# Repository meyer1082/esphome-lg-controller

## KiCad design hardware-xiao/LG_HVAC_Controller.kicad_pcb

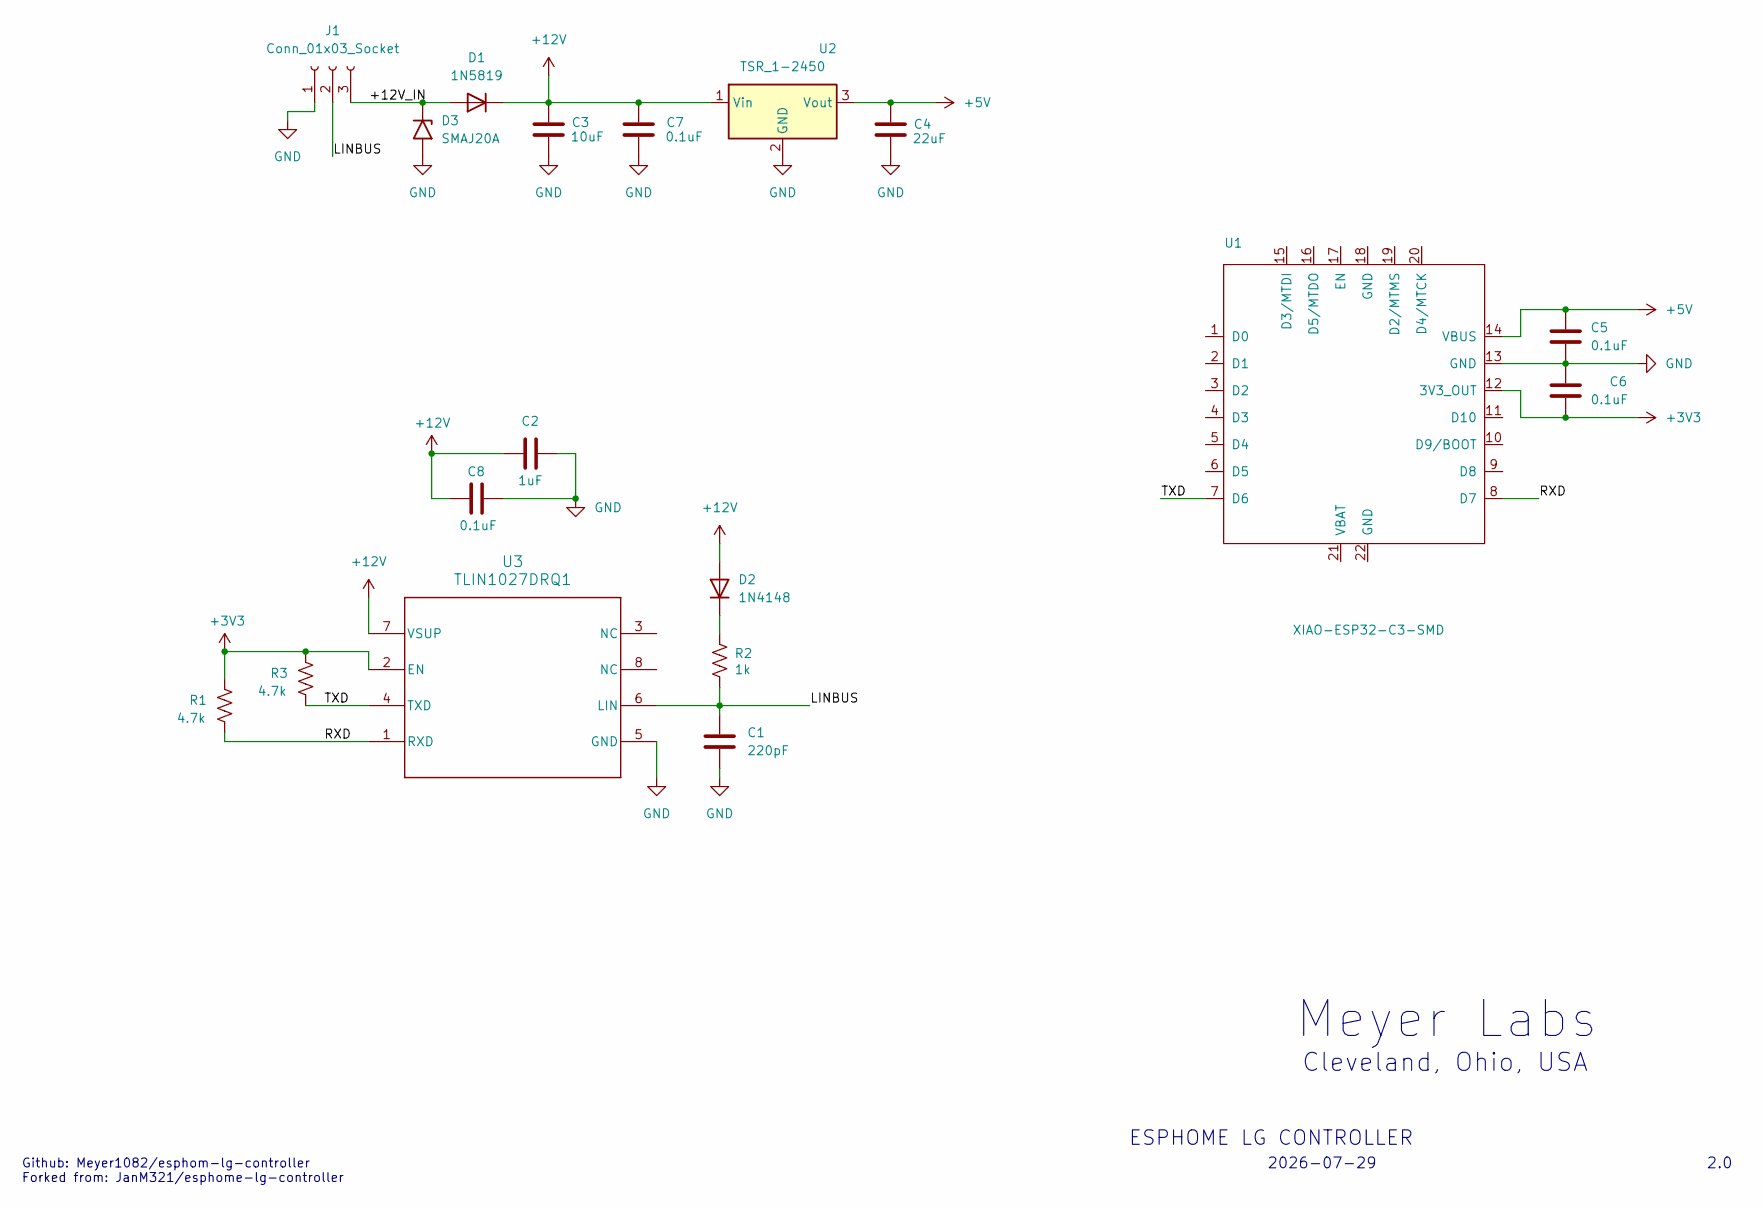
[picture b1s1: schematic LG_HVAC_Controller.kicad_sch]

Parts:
C1: 220pF; C_0805_2012Metric_Pad1.18x1.45mm_HandSolder
C2: 1uF; C_0805_2012Metric_Pad1.18x1.45mm_HandSolder
C3: 10uF; C_1210_3225Metric_Pad1.33x2.70mm_HandSolder
C4: 22uF; C_1210_3225Metric_Pad1.33x2.70mm_HandSolder
C5, C6, C7, C8: 0.1uF; C_0805_2012Metric_Pad1.18x1.45mm_HandSolder
D1: 1N5819; D_SOD-123
D2: 1N4148; D_SOD-123
D3: SMAJ20A; D_SMA_Handsoldering
J1: Conn_01x03_Socket; JST_XH_S3B-XH-A_1x03_P2.50mm_Horizontal
R1, R3: 4.7k; R_0805_2012Metric_Pad1.20x1.40mm_HandSolder
R2: 1k; R_0805_2012Metric_Pad1.20x1.40mm_HandSolder
U1: XIAO-ESP32-C3-SMD
U2: TSR_1-2450; Converter_DCDC_TRACO_TSR-1_THT
U3: TLIN1027DRQ1; D0008B_L

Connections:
+3V3: C6.1, R1.1, R3.1, U1.12 (3V3_OUT), U3.2 (EN)
+5V: C4.2, C5.2, U1.14 (VBUS), U2.3 (Vout)
+12V: C2.1, C3.2, C7.2, C8.2, D1.1 (K), D2.2 (A), U2.1 (Vin), U3.7 (VSUP)
/+12V_IN: D1.2 (A), D3.1 (A1), J1.3
/LINBUS: C1.1, J1.2, R2.2, U3.6 (LIN)
/RXD: R1.2, U1.8 (D7), U3.1 (RXD)
/TXD: R3.2, U1.7 (D6), U3.4 (TXD)
GND: C1.2, C2.2, C3.1, C4.1, C5.1, C6.2, C7.1, C8.1, D3.2 (A2), J1.1, U1.13 (GND), U2.2 (GND), U3.5 (GND)
unnamed: D2.1 (K), R2.1

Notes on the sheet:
Meyer Labs
2026-07-29
ESPHOME LG CONTROLLER
Cleveland, Ohio, USA
2.0
Github: Meyer1082/esphom-lg-controller Forked from: JanM321/esphome-lg-controller

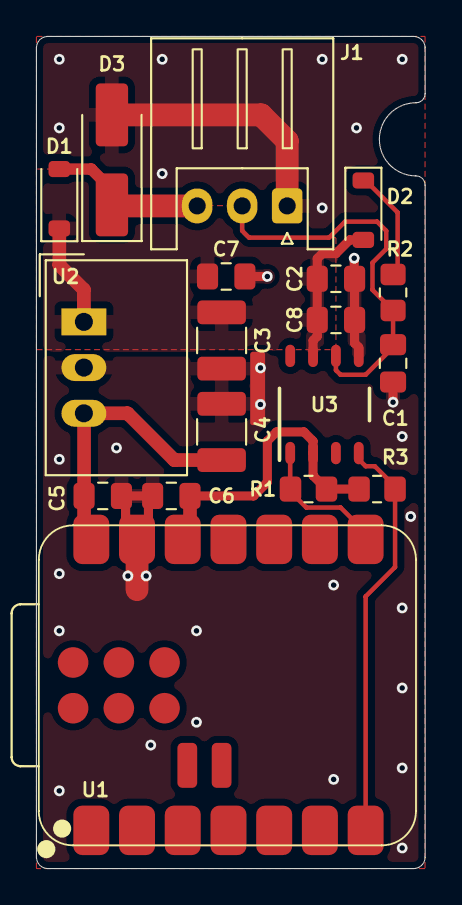
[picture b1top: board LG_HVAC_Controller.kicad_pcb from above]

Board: 2 copper layers, 21.6 x 46.2 mm, 18 parts (0 on the bottom side), 9 nets.
